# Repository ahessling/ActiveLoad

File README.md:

# Active Load with microcontroller
This repository contains the hardware design, the firmware and the GUI software of my active load device.

Features:
* Power supply from around 3.3V to 40V
* Should be powered by device under test
* Alternative power supply via USB
* Maximum dissipated power: Around 12W permanently at room temperature
* Maximum current: 3A
* Robust (protected from overvoltage, overcurrent and overtemperature conditions)
* Device under test should be connected via banana plugs or screw terminals
* A PC should be able to monitor the actual current and control the desired current via USB
* Small display to monitor actual and setpoint current
* Rotary encoder to change setpoint current
* Small (5×10 cm)
* Measure temperature at heatsink

The whole design process with a lot of details are written down [in my blog](http://blog.andrehessling.de/2016/02/07/project-active-load-with-microcontroller-part-1-requirements/).

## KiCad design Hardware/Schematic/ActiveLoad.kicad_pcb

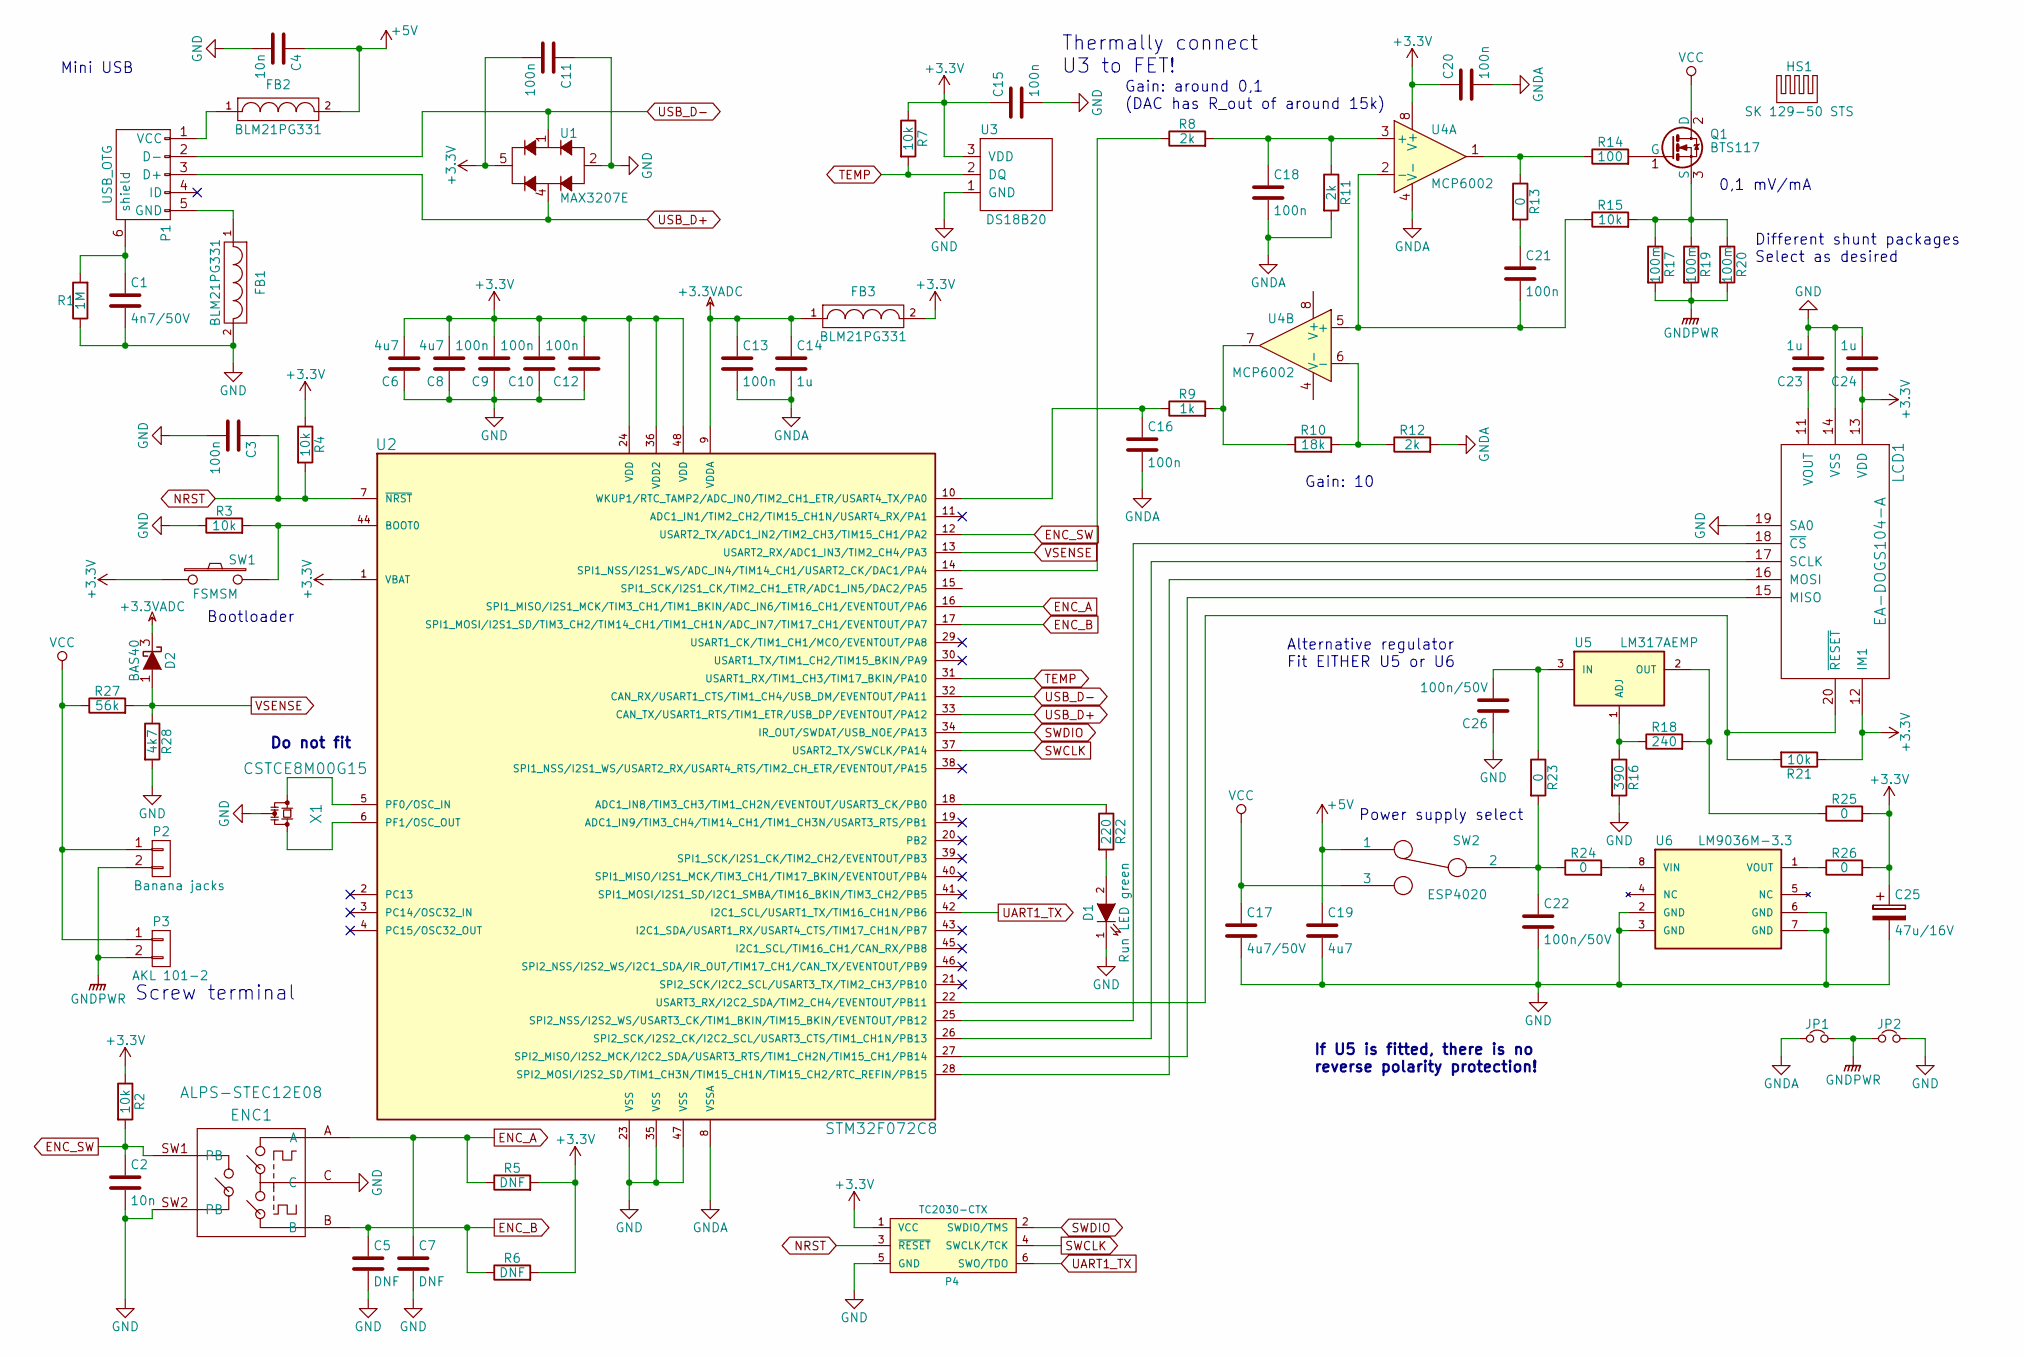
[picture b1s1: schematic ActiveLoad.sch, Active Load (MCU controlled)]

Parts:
C1: 4n7/50V; C_1210
C2, C4: 10n; C_0603
C3, C9, C10, C11, C12, C13, C15, C16, C18, C20, C21: 100n; C_0603
C5, C7: DNF; C_0603
C6, C8, C19: 4u7; C_0805
C14, C23, C24: 1u; C_0603
C17: 4u7/50V; C_1206
C22, C26: 100n/50V; C_0805
C25: 47u/16V; c_elec_6.3x5.3
D1: Run LED green; LED_0603
D2: BAS40; SOT-23
ENC1: ALPS-STEC12E08
FB1, FB2, FB3: BLM21PG331; R_0805
HS1: SK 129-50 STS; Heatsink_Fischer_SK129-STS_42x25mm_2xDrill2.5mm
JP1, JP2: Jumper_NC_Small; NetTie-I_Connected_SMD
LCD1: EA-DOGS104-A; DOGS104
P1: USB_OTG; USB_Mini-B
P2: Banana jacks; Banana_Jack_2Pin
P3: AKL 101-2; mors_2p
P4: TC2030-CTX; TC2030_SMALL
Q1: BTS117; TO-220_Neutral123_Vertical
R1: 1M; R_1206
R2, R3, R4, R7, R15, R21: 10k; R_0603
R5, R6: DNF; R_0603
R8, R11, R12: 2k; R_0603
R9: 1k; R_0603
R10: 18k; R_0603
R13, R23, R24, R25, R26: 0; R_0603
R14: 100; R_0603
R16: 390; R_0603
R17, R20: 100m; R_2512
R18: 240; R_0603
R19: 100m; Resistor_Cement_Horizontal_Meggitt-SBC-2
R22: 220; R_0603
R27: 56k; R_0603
R28: 4k7; R_0603
SW1: FSMSM; SW_SPST_FSMSM
SW2: ESP4020; ESP40XX
U1: MAX3207E; SOT-23-6
U2: STM32F072C8; LQFP-48_7x7mm_Pitch0.5mm
U3: DS18B20; TO-92_Inline_Narrow_Oval
U4: MCP6002; SOIC-8_3.9x4.9mm_Pitch1.27mm
U5: LM317AEMP; SOT-223
U6: LM9036M-3.3; SOIC-8_3.9x4.9mm_Pitch1.27mm
X1: CSTCE8M00G15; CSTCE_G15C

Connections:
+3.3VADC: C13.1, C14.1, D2.3 (K), FB3.1, U2.9 (VDDA)
+3V3: C6.2, C8.2, C9.2, C10.2, C11.2, C12.2, C15.1, C20.1, C24.1, C25.1, FB3.2, LCD1.12 (IM1), LCD1.13 (VDD), P4.1 (VCC), R2.1, R4.1, R5.2, R6.2, R7.1, R21.1, R25.2, R26.2, SW1.1, U1.5 (VCC), U2.1 (VBAT), U2.24 (VDD), U2.36 (VDD2), U2.48 (VDD), U3.3 (VDD), U4.8 (V+)
+5V: C4.1, C19.1, FB2.2, SW2.1
ENC_A: C7.1, ENC1.A, R5.1, U2.16 (SPI1_MISO/I2S1_MCK/TIM3_CH1/TIM1_BKIN/A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)
ENC_B: C5.1, ENC1.B, R6.1, U2.17 (SPI1_MOSI/I2S1_SD/TIM3_CH2/TIM14_CH1/TI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)
ENC_SW: C2.1, ENC1.SW1 (PB), R2.2, U2.12 (USART2_TX/ADC1_IN2/TIM2_CH3/TIM15_CH1/P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)
GND: C1.2, C2.2, C3.2, C4.2, C5.2, C6.1, C7.2, C8.1, C9.1, C10.1, C11.1, C12.1, C15.2, C17.2, C19.2, C22.2, C23.2, C24.2, C25.2, C26.1, D1.1 (K), ENC1.C, ENC1.SW2 (PB), FB1.2, JP2.2, LCD1.14 (VSS), LCD1.19 (SA0), P4.5 (GND), R1.1, R3.1, R16.2, R28.2, U1.2 (GND), U2.23 (VSS), U2.35 (VSS), U2.47 (VSS), U3.1 (GND), U6.2 (GND), U6.3 (GND), U6.6 (GND), U6.7 (GND), X1.2
GNDA: C13.2, C14.2, C16.2, C18.2, C20.2, JP1.1, R11.2, R12.2, U2.8 (VSSA), U4.4 (V-)
GNDPWR: JP1.2, JP2.1, P2.2, P3.2, R17.2, R19.2, R20.2
NRST: C3.1, P4.3 (~RESET~), R4.2, U2.7 (~NRST)
unnamed: C1.1, P1.6 (shield), R1.2
unnamed: C16.1, R9.1, U2.10 (WKUP1/RTC_TAMP2/ADC_IN0/TIM2_CH1_ETR/US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)
unnamed: C18.1, R8.2, R11.1, U4.3 (+)
unnamed: C21.1, R13.2
unnamed: C21.2, R15.1, U4.2 (-), U4.5 (+)
unnamed: C22.1, R23.2, R24.1, SW2.2
unnamed: C23.1, LCD1.11 (VOUT)
unnamed: C26.2, R23.1, U5.3 (IN)
unnamed: D1.2 (A), R22.2
unnamed: FB1.1, P1.5 (GND)
unnamed: FB2.1, P1.1 (VCC)
unnamed: LCD1.15 (MISO), U2.27 (SPI2_MISO/I2S2_MCK/I2C2_SDA/USART3_RTS/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)
unnamed: LCD1.16 (MOSI), U2.28 (SPI2_MOSI/I2S2_SD/TIM1_CH3N/TIM15_CH1N/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)
unnamed: LCD1.17 (SCLK), U2.26 (SPI2_SCK/I2S2_CK/I2C2_SCL/USART3_CTS/TI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)
unnamed: LCD1.18 (~CS~), U2.25 (SPI2_NSS/I2S2_WS/USART3_CK/TIM1_BKIN/TI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)
unnamed: LCD1.20 (~RESET~), R21.2, U2.22 (USART3_RX/I2C2_SDA/TIM2_CH4/EVENTOUT/PB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)
unnamed: Q1.1 (G), R14.2
unnamed: Q1.3 (S), R15.2, R17.1, R19.1, R20.1
unnamed: R3.2, SW1.2, U2.44 (BOOT0)
unnamed: R8.1, U2.14 (SPI1_NSS/I2S1_WS/ADC_IN4/TIM14_CH1/USAR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)
unnamed: R9.2, R10.1, U4.7
unnamed: R10.2, R12.1, U4.6 (-)
unnamed: R13.1, R14.1, U4.1
unnamed: R16.1, R18.1, U5.1 (ADJ)
unnamed: R18.2, R25.1, U5.2 (OUT)
unnamed: R22.1, U2.18 (ADC1_IN8/TIM3_CH3/TIM1_CH2N/EVENTOUT/US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)
unnamed: R24.2, U6.8 (VIN)
unnamed: R26.1, U6.1 (VOUT)
unnamed: U2.5 (PF0/OSC_IN), X1.1
unnamed: U2.6 (PF1/OSC_OUT), X1.3
SWCLK: P4.4 (SWCLK/TCK), U2.37 (USART2_TX/SWCLK/PA14)
SWDIO: P4.2 (SWDIO/TMS), U2.34 (IR_OUT/SWDAT/USB_NOE/PA13)
TEMP: R7.2, U2.31 (USART1_RX/TIM1_CH3/TIM17_BKIN/PA10), U3.2 (DQ)
UART1_TX: P4.6 (SWO/TDO), U2.42 (I2C1_SCL/USART1_TX/TIM16_CH1N/PB6)
USB_D+: P1.3 (D+), U1.4 (I/O2), U2.33 (CAN_TX/USART1_RTS/TIM1_ETR/USB_DP/EVENT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)
USB_D-: P1.2 (D-), U1.1 (I/O1), U2.32 (CAN_RX/USART1_CTS/TIM1_CH4/USB_DM/EVENT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)
VCC: C17.1, P2.1, P3.1, Q1.2 (D), R27.1, SW2.3
VSENSE: D2.1 (A), R27.2, R28.1, U2.13 (USART2_RX/ADC1_IN3/TIM2_CH4/PA3)

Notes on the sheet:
Mini USB
Bootloader
0,1 mV/mA
Gain: 10
Gain: around 0,1 (DAC has R_out of around 15k)
Screw terminal
Thermally connect U3 to FET!
Alternative regulator Fit EITHER U5 or U6
Different shunt packages Select as desired
Power supply select
If U5 is fitted, there is no reverse polarity protection!
Do not fit

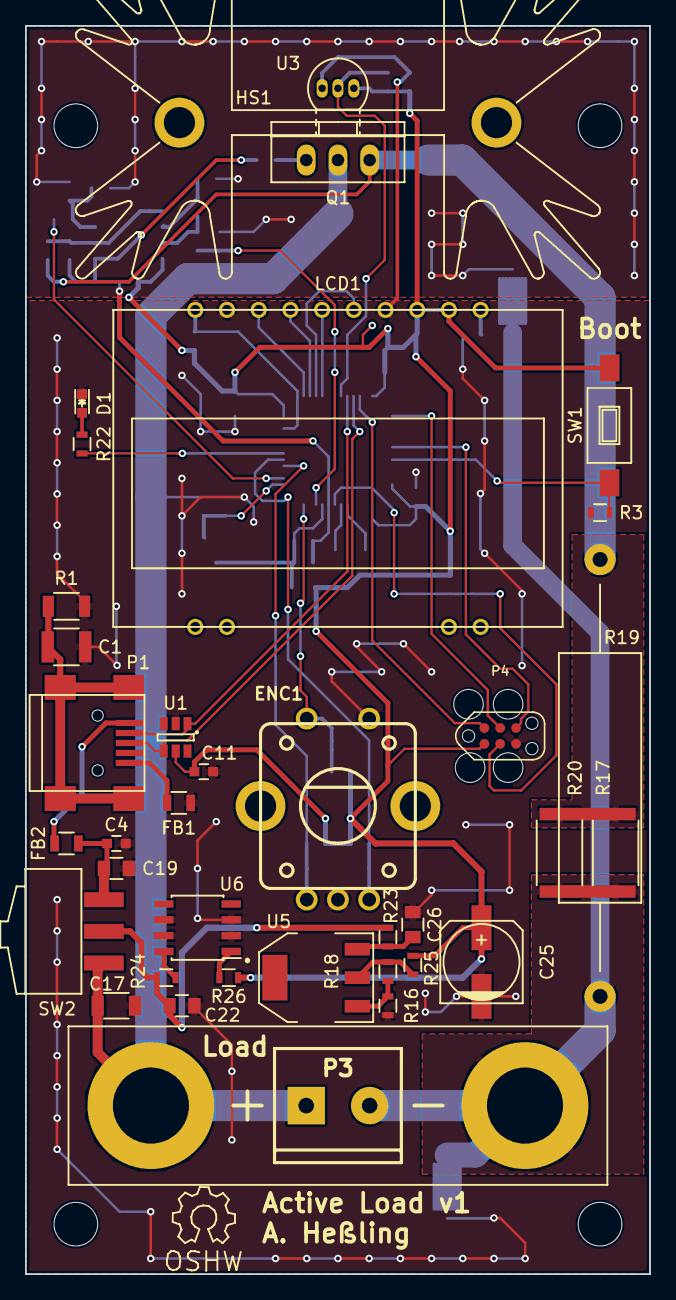
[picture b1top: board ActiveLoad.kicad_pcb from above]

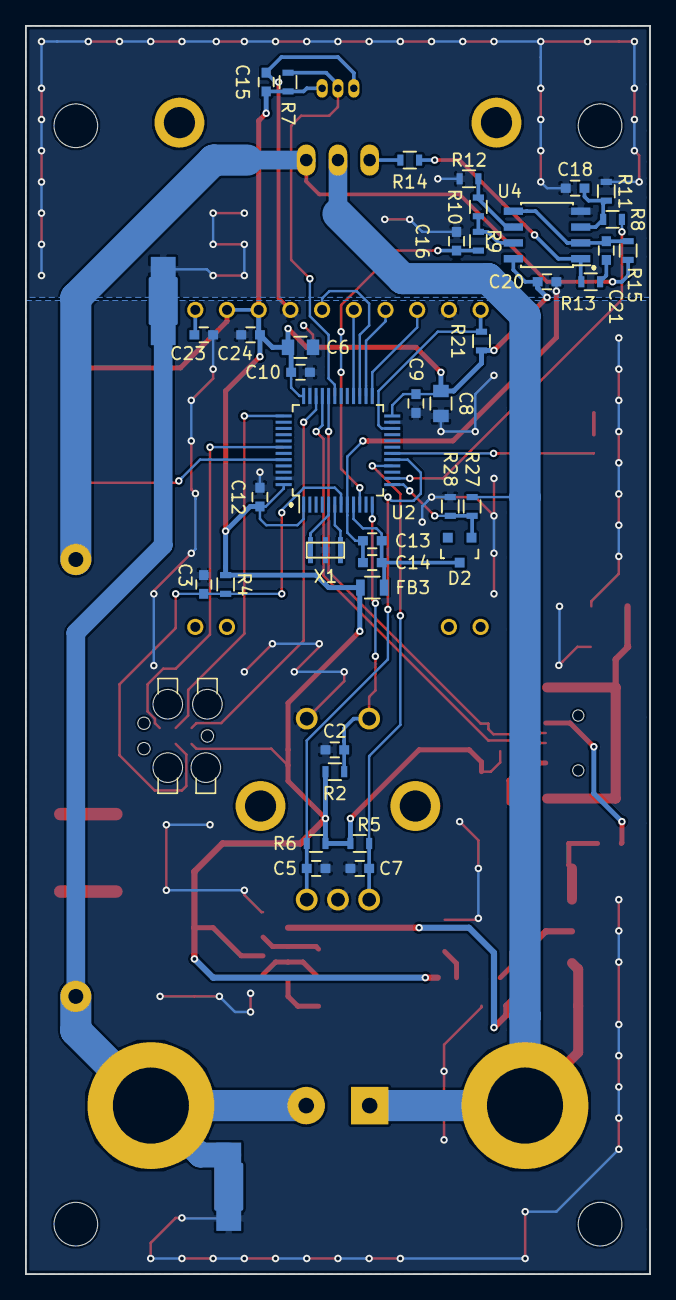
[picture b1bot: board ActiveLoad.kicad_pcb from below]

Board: 2 copper layers, 50.0 x 100.0 mm, 78 parts (41 on the bottom side), 48 nets.

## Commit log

2016-01-17 feat: created KiCAD base project
2016-01-17 feat: added devices BTS117, LM9036M and STM32F072C8
2016-02-01 updated schematic
2016-02-02 updated schematic added DOG display library
2016-02-04 (nearly) finished schematic
2016-02-05 finished schematic
2016-02-06 updated schematic PCB work
2016-02-07 updated schematic (TEMP pin and LED pin) finished PCB
2016-02-07 updated schematic and PCB (added VSENSE)
2016-02-08 changed Gerber export settings PCB finished and exported
2016-02-12 fix: changed R8 and R11 to 18k and 2k to get a gain of 0,1
2016-02-13 feat: initial commit of firmware
2016-02-14 feat: prepare encoder interface
2016-02-15 feat: encoder working with differen timer clock settings and filter, debug output code for now
2016-02-16 fix: need to reset USB CDC transfer state if connection to host is established or removed
2016-02-18 feat: new function stepSetpointCurrent to step up/down setpoint current feat: encoder steps are evaluated and setpoint current changes accordingly fix: needed mA to A conversion in HMI_USB fix: setpo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
2016-02-18 feat: implemented actual voltage calibration
2016-02-18 feat: implemented actual/setpoint current calibration
2016-02-18 feat: memory slots can be read from flash feat: parameter section in flash (at the end)
2016-02-19 feat: parameters can be read from flash and written to flash refactor: CRC16 initial value should be 0xFFFF instead of 0xFF
2016-02-20 fix: calculation of buffer size of "savedParameters" was wrong
2016-02-24 feat: display write routines to write whole strings to display
2016-02-24 feat: initial commit of DOGS104 with SPI interface feat: gpio.h helper struct to integrate a GPIO port and pin
2016-02-24 feat: HMI_Front module now includes DOGS104_SPI device
2016-02-25 feat: actual power is calculated feat: overloaded relational operators == and != of SystemState
2016-02-25 feat: display is updated when the system state changes (but only every 100 ms) feat: printf can now use floats
2016-02-28 refactor: use MCP6002 (and not MCP6442 which does NOT have a better performance) fix: replaced 8,2µH/0805 inductors with BLM21PG331 EMI ferrite filters
2016-03-01 feat: LCD now supports double buffering using a framebuffer feat: only the changed data are written when double buffering is enabled
2016-03-01 fix: need a copy of _gpioReset and not a reference since it gets out of scope
2016-03-01 chore: add --specs=nosys.specs to Makefile
2016-03-02 fix: cursor must be manually moved to new lines if the framebuffer is written to the LCD memory due to the addressing scheme
2016-03-02 fix: cursor position needed to be set to zero if display is cleared refactor: DOG display lines now configurable from 1 to 4 fix: reworked the LCD init function to (hopefully) set all registers corre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
2016-03-03 fix: _ebss should be _end because of "noinit" section between _ebss and _end
2016-03-06 feat: initial commit of C# library "ActiveLoadProtocol" and class "SerialPortBuffered" as a wrapper of .NET's SerialPort component
2016-03-07 chore: added .gitignore and .gitattributes
2016-03-07 refactor: renamed functions feat: initial commit of classes ASCIIRequestResponse and ActiveLoadDevice
2016-03-08 feat: added SimpleSCPIProtocol and interface IASCIIReadWrite refactor: make ASCIIRequestResponse dependent on interface IASCIIReadWrite feat: SerialPortBuffered implements interface IASCIIReadWrite
2016-03-08 feat: do not receive asynchronously per default, it must be explicitly enabled now via property AsyncReceive feat: experiments with function ReadUntil
2016-03-09 feat: ReadUntil now working with timeout check
2016-03-09 refactor: add Async suffix to function name feat: Also flush internal serial port buffer
2016-03-09 refactor: interface IASCIIReadWrite extended with ReadUntilAsync refactor: replace EndWithNewLine with EndLineSuffix to be more general refactor: smaller timeout feat: make all functions which read s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
2016-03-13 refactor: add Async suffix to functions feat: add helper function CommandAsync with demanded response (throw exception if response differs)
2016-03-13 cleanup: remove asyncReceive functions feat: add ReadAsync wrapper function
2016-03-13 feat: added getter functions to read system state of device feat: added setter functions to set system state of device feat: added function to find all active load devices
2016-03-13 fix: device was not always being closed while searching for a device
2016-03-17 fix: disable DAC output buffer because of minimum low output voltage (~200 mV). Output impedance is around 15k which means that the voltage divider may need adjustment.
2016-03-18 fix: because no HSE is used in default hardware variant, HSI48 needs to be enabled. Otherwise the CPU runs at 8 MHz
2016-03-18 fix: display turn on command was wrong feat: clear display on init
2016-03-18 refactor: change reset delay to 20 ms feat: support for display read operation fix: completely wrong SPI data format: LSB first and 3 bytes per transfer needed fix: after calling spi.reconfigure, eve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
2016-03-19 fix: reconfigure SPI by resetting the peripheral via RCC command fix: deinit should disable the peripheral clock
2016-03-19 refactor: spi.reconfigure is now called again
2016-03-19 fix: start of application should be delayed so that LCD can power up
2016-03-19 doc: added function description
2016-03-19 change: output string of measured voltage
2016-03-19 feat: initial temperature reading when application starts
2016-03-20 fix: setpoint and actual current cannot be negative (can happen if calibrated)
2016-03-20 feat: SCPI DUMP? request to dump system state
2016-03-20 fix: SystemCommand did not load NVRAM settings
2016-03-20 fix: due to internal resistance of unbuffered DAC output (~15k), R8 is lowered to 2k
2016-03-21 feat: added function to set new setpoint current while taking system limits into account feat: output "value out of range error" if an invalid setpoint current is given via USB
2016-03-21 feat: minimize current draw if setpoint current is 0 by switching DAC off
2016-03-21 feat: detect overtemperature condition if temperature is above 70 degree Celsius feat: blink last display line during overtemperature conditions cleanup: remove _lastSystemState and update display ev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
2016-03-21 feat: LED shows system state (blinks slowly if setpoint and actual current differ, blinks fast when overtemperature)
2016-03-22 feat: if encoder key is pressed, reset to safe state (setpoint current to 0)
2016-03-22 doc: added note that LM317 has no reverse polarity protection
2016-03-23 feat: DS18x20 ROM code can be read feat: DS18B20 class also supports DS18S20 feat: DS18x20 type auto detection
2016-03-23 feat: unknown/invalid temperatures are now displayed as "?" fix: correct rounding using roundf feat: MEAS:TEMP? now displays temperature with one decimal place
2016-03-23 refactor: set USB buffer size to 1024
2016-03-23 feat: add MEAS:POWer? query to get actual power and also add actual power to DUMP?
2016-03-24 fix: missing include
2016-03-24 feat: TwoPointCalibration now includes input and output vector which was used for calibration
2016-03-24 refactor: changed NVRAM layout due to new TwoPointCalibration representation
2016-03-24 change: SCPI subsystem CALIB is now CAL feat: CAL:CURR? and CAL:VOLT? queries added to get details about the calibration data feat: CAL:CLEAR ALL, CAL:CLEAR VOLT and CAL:CLEAR CURR to selectively cle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
2016-03-24 fix: *RST should at least put the system into a safe state chore: set version to 0.9-1
2016-03-24 fix: make changing of output current depend on calibrated current and not on setpoint current cleanup: _oldSystemState not needed chore: revision to 2
2016-03-25 chore: change some resistors, caps and resonator to "DNF"
2016-03-25 feat: encoder key now retrieves old setpoint current if it is pressed again chore: revision to 3
2016-03-26 feat: added functions GetSetpointCurrentAsync, GetDissipatedPowerAsync and BootloaderAsync feat: SCPI identity object is parsed and saved feat: SCPI identity object as public property
2016-03-26 feat: added calibration functions
2016-03-27 doc: added comments
2016-03-27 feat: added property IsOpen refactor: change name Open to OpenAsync refactor: OpenAsync now returns the SCPI identity object. This means that an exception is thrown if the device to be opened is not 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
2016-03-27 feat: initial commit of Active Load Tool
2016-03-30 fix: await cancellation only if cancellation token exists
2016-03-30 fix: InvariantCulture needed while parsing numbers with a decimal dot/comma
2016-03-30 refactor: return null as temperature if device cannot read the current temperature (it returns a ? in this case)
2016-03-30 refactor: rename Send to SendAsync and make it an async function refactor: make all Send functions async fix: use semaphore in "request response protocol" to avoid starting a new request while still 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
2016-03-30 feat: added property Overtemperature to indicate an overtemperature condition
2016-03-30 feat: added controls to visualize and control state of device feat: exceptions are now evaluated and proper error messages are generated
2016-03-30 doc: added property docs fix: retry once while trying to get identity object. Otherwise connect might fail sometimes, this is just a workaround because the problem is in the device firmware.
2016-03-30 clean: remove debug line
2016-03-31 feat: it is now checked if device is calibrated when the connection has been established
2016-03-31 feat: warning is displayed if device is not calibrated fix: no need to await cancellation if disconnect button is pressed
2016-03-31 refactor: rename activeLoadCancellationTokenSource to ctsRefreshTask fix: produce error in message box only if an unexpected error happened fix: no need to wait for cancellation feat: disable button 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
2016-03-31 feat: class CalibrationData with subclasses CurrentCalibration and VoltageCalibration refactor: all format specific conversions done in Calibration subclasses refactor: function GetCalibrationAsync n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
2016-03-31 feat: last COM port with a valid connection is saved and loaded
2016-04-01 refactor: change response timeout to 250 ms
2016-04-01 feat: make last seen voltage and current available as properties refactor: make calibration data points public
2016-04-01 feat: calibration now possible via tool and extra form
2016-04-01 fix: flush buffers by sending an empy SCPI line and await answer when device is opened fix: SCPI identity object should be dissected in try-catch block
2016-04-01 fix: cancel refresh task when form is closing
2016-04-03 feat: added property (last seen) Temperature
2016-04-03 feat: initial commit of oscilloscope-like graph form
2016-04-03 fix: chart bounds were not recalculated when interval had changed
2016-04-03 feat: enable watchdog chore: set version to 1.0-1
2016-04-03 feat: added an AboutBox chore: updated assembly info
2016-04-04 chore: set Doxygen package name correctly
2016-04-08 chore: added LICENSE
2016-04-08 doc: README added
2016-04-08 chore: added firmware binary 1.0-1
2016-05-02 fix: temporarily disable the USB interrupt while communicating with the temperature sensor because it might disturb the one-wire communication
2016-05-02 chore: added firmware binary 1.0-2
2016-07-02 doc: added picture of finished hardware
2016-07-02 doc: update README to inclue picture
2020-02-08 doc: add pdf schematic
